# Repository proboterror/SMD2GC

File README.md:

# Sega Mega Drive to GameCube controller adapter

Also supports Xbox controllers (Xbox 360 / One / Series) and standard USB HID gamepads (with layout similar to PS4 DualShock 4) with USB Type-C OTG adapter.

USB gamepads support can be limited because of GameCube controller port does not provide sufficient +5V power (PS5 DualSense not working).

Bluetooth dongles are not supported unless they emulate standard USB HID device.

DualShock 3 / DualShock 4 / Xbox One / Series controllers are recommended.

Tested with USB controlers:

|Model|State|
|-----|-----|
|Xbox 360 USB|Working|
|Xbox One Model 1537|Working|
|Xbox Series Model 1914|Working|
|PS3 DualShock 3 CECHZC2R|Working|
|PS4 DualShock 4 CUH-ZCT1E|Working|
|PS5 DualSense CFI-ZCT1W|Not working<br>Unsufficient power|

## Schematics

## Bill of Materials
- GameCube controller replacement cable
- WaveShare RP2040-Zero board
- DB9 Male connector
- 12 wires (approx. 60 mm each); 3 wires for USB pads only

## Buttons mapping
A/B, X/Y buttons mapping for USB gamepads matches Xbox controllers layout (reverse SNES A/B, X/Y).

### Sega Mega Drive 6-button pad
src/main.cpp:
```
gc.a = smd.a;
gc.b = smd.b;
gc.x = smd.x;
gc.y = smd.y;

gc.l = smd.z;
gc.r = smd.c;

gc.start = smd.start;

gc.dLeft = smd.left;
gc.dRight = smd.right
gc.dDown = smd.down
gc.dUp = smd.up
gc.z = smd.mode
```
### Xbox controllers
src/main.c:
```
gc.a = (buttons & XINPUT_GAMEPAD_A);
gc.b = (buttons & XINPUT_GAMEPAD_B);
gc.x = (buttons & XINPUT_GAMEPAD_X);
gc.y = (buttons & XINPUT_GAMEPAD_Y);

gc.start = (buttons & (XINPUT_GAMEPAD_START | XINPUT_GAMEPAD_GUIDE));

gc.dLeft = (buttons & XINPUT_GAMEPAD_DPAD_LEFT);
gc.dRight = (buttons & XINPUT_GAMEPAD_DPAD_RIGHT);
gc.dDown = (buttons & XINPUT_GAMEPAD_DPAD_DOWN);
gc.dUp = (buttons & XINPUT_GAMEPAD_DPAD_UP);

const uint8_t TRIGGER_CLICK_TRESHOLD = 32;
gc.l = pad->bLeftTrigger > TRIGGER_CLICK_TRESHOLD
gc.r = pad->bRightTrigger > TRIGGER_CLICK_TRESHOLD;

gc.z = (buttons & XINPUT_GAMEPAD_RIGHT_SHOULDER);

gc.xStick = int16_to_u8_biased(pad->sThumbLX);
gc.yStick = int16_to_u8_biased(pad->sThumbLY);

gc.cxStick = int16_to_u8_biased(pad->sThumbRX);
gc.cyStick = int16_to_u8_biased(pad->sThumbRY);

gc.analogL = pad->bLeftTrigger;
gc.analogR = pad->bRightTrigger;
```

### Standard USB HID controllers (DualShock 4)
src/hid_gamecube_mapping.cpp:
```
REPORT_USAGE_PAGE_BUTTON, 1, MAP_GAMECUBE_BUTTON_X // Square -> X
REPORT_USAGE_PAGE_BUTTON, 2, MAP_GAMECUBE_BUTTON_A // Cross -> A
REPORT_USAGE_PAGE_BUTTON, 3, MAP_GAMECUBE_BUTTON_B // Circle -> B
REPORT_USAGE_PAGE_BUTTON, 4, MAP_GAMECUBE_BUTTON_Y // Triangle -> Y

REPORT_USAGE_PAGE_BUTTON, 6, MAP_GAMECUBE_BUTTON_Z // R1

// Note: DualShock S4 generates press event starting from minimum force,
// GameCube controller generates L/R clicks after maximum force to analog L/R axes applied.
// Can be replaced with mapping analog Rx/Ry axis with MAP_TYPE_THRESHOLD_ABOVE 192 (75%) to GameCube L/R.
REPORT_USAGE_PAGE_BUTTON, 7, MAP_GAMECUBE_BUTTON_L // L2 Digital
REPORT_USAGE_PAGE_BUTTON, 8, MAP_GAMECUBE_BUTTON_R // R2 Digital

REPORT_USAGE_PAGE_BUTTON, 10, MAP_GAMECUBE_BUTTON_START // Options -> Start

// Left analog
REPORT_USAGE_X, MAP_GAMECUBE_AXIS_X // LX
REPORT_USAGE_Y, MAP_GAMECUBE_AXIS_Y // LY, inverted
// Right analog
REPORT_USAGE_Z, MAP_GAMECUBE_AXIS_CX // RX 
REPORT_USAGE_Rz, MAP_GAMECUBE_AXIS_CY // RY, inverted
// Analog left/right triggers
REPORT_USAGE_Rx, MAP_GAMECUBE_AXIS_L // LT / R2
REPORT_USAGE_Ry, MAP_GAMECUBE_AXIS_R // RT / R2

// POV/HAT switch (also D-PAD in most cases)
// 0 on hat switch, just press up
MAP_GAMECUBE_U, HID_GAMEPAD_HAT_UP
// 1 on hat switch, press up and right
HID_GAMEPAD_HAT_UP_RIGHT, MAP_GAMECUBE_U
HID_GAMEPAD_HAT_UP_RIGHT, MAP_GAMECUBE_R
// 2 on hat switch, press right
HID_GAMEPAD_HAT_RIGHT, MAP_GAMECUBE_R
// 3 on hat, press right and down
HID_GAMEPAD_HAT_DOWN_RIGHT, MAP_GAMECUBE_R
HID_GAMEPAD_HAT_DOWN_RIGHT, MAP_GAMECUBE_D
// 4 on hat, press down
HID_GAMEPAD_HAT_DOWN, MAP_GAMECUBE_D
// 5 on hat, press down and left
HID_GAMEPAD_HAT_DOWN_LEFT, MAP_GAMECUBE_D
HID_GAMEPAD_HAT_DOWN_LEFT, MAP_GAMECUBE_L
// 6 on hat, press left
HID_GAMEPAD_HAT_LEFT, MAP_GAMECUBE_L
// 7 on hat, press left and up
HID_GAMEPAD_HAT_UP_LEFT, MAP_GAMECUBE_L
HID_GAMEPAD_HAT_UP_LEFT, MAP_GAMECUBE_U

// Rarely used
REPORT_USAGE_DPAD_UP, MAP_GAMECUBE_U
REPORT_USAGE_DPAD_DOWN, MAP_GAMECUBE_D
REPORT_USAGE_DPAD_RIGHT, MAP_GAMECUBE_R
REPORT_USAGE_DPAD_LEFT, MAP_GAMECUBE_L

PS4 DualShock 4 / PS5 DualSense used as reference for buttons IDs:
Button 0x01 - Square button
Button 0x02 - Cross button
Button 0x03 - Circle button
Button 0x04 - Triangle button
Button 0x05 - L1 button
Button 0x06 - R1 button
Button 0x07 - L2 button
Button 0x08 - R2 button
Button 0x09 - Share button
Button 0x0A - Options button
Button 0x0B - L3 button
Button 0x0C - R3 button
Button 0x0D - PS button
Button 0x0E - Touchpad button
```

### DualShock 3
```
gc.a = ps3->button_cross;
gc.b = ps3->button_circle;
gc.x = ps3->button_square;
gc.y = ps3->button_triangle;
gc.start = ps3->button_start;

gc.dLeft = ps3->dpad_left;
gc.dRight = ps3->dpad_right;
gc.dDown = ps3->dpad_down;
gc.dUp = ps3->dpad_up;

const uint8_t TRIGGER_CLICK_TRESHOLD = 32;
gc.l = ps3->trigger_l2_analog > TRIGGER_CLICK_TRESHOLD;
gc.r = ps3->trigger_r2_analog > TRIGGER_CLICK_TRESHOLD;

gc.z = ps3->trigger_r1;

gc.xStick = ps3->joy_left_x;
gc.yStick = UINT8_MAX - ps3->joy_left_y;
gc.cxStick = ps3->joy_right_x;
gc.cyStick = UINT8_MAX - ps3->joy_right_y;
gc.analogL = ps3->trigger_l2_analog;
gc.analogR = ps3->trigger_r2_analog;
```

## Input lag / latency
For Sega Mega Drive 6 buttons pad delay mostly defined by GameCube controller JoyBus speed if queried once per frame:<br>
3 bytes console request + 8 bytes response @250kbps: protocol delay ~0.35 ms.

USB pads are reports its state at fixed rate, mostly 125Hz (8 ms latency).<br>
DualShock 4 has a default wired polling rate 250Hz (4ms latency)<br>
Xbox Series Controller Model 1914: default USB poll rate 125Hz (8 ms latency)

## How to flash firmware
- Connect RP2040-Zero to PC
- Press BOOT and then RESET, new drive will appear
- Drop SMD2GC.uf2 from Releases section to new drive

## How to build firmware
Checkhout git repository.
```
git submodule update --init
```
Easy way:
- Install Visual Studio Code and official Raspberry Pi Pico Visual Studio Code extension
- On "Raspberry Pi Pico Project" left tab: "Import project"
- "Configure Cmake", use toolchain installed with Raspberry Pi Pico Visual Studio Code extension
- "Compile Project"
- "Run Project (USB)". Board should be in BOOT mode.

Hard way:
- Install Raspberry Pi Pico SDK, ARM-GCC toolchain, CMake.

## Credits
- [Julien Bernard](https://github.com/JulienBernard3383279/pico-rectangle) - Joybus protocol (Gamecube controller) implementation for the Raspberry Pi Pico
- [riguetti](https://github.com/riguetti/RP2040-Zero-gamecube-controller) - unused code cleanup
- [Andrew Tait](https://github.com/rasteri/HIDman) - USB HID descriptors and reports parsing code
- [Ryzee119](https://github.com/Ryzee119/tusb_xinput) - Xbox/Xinpit controllers support module for TinyUSB library

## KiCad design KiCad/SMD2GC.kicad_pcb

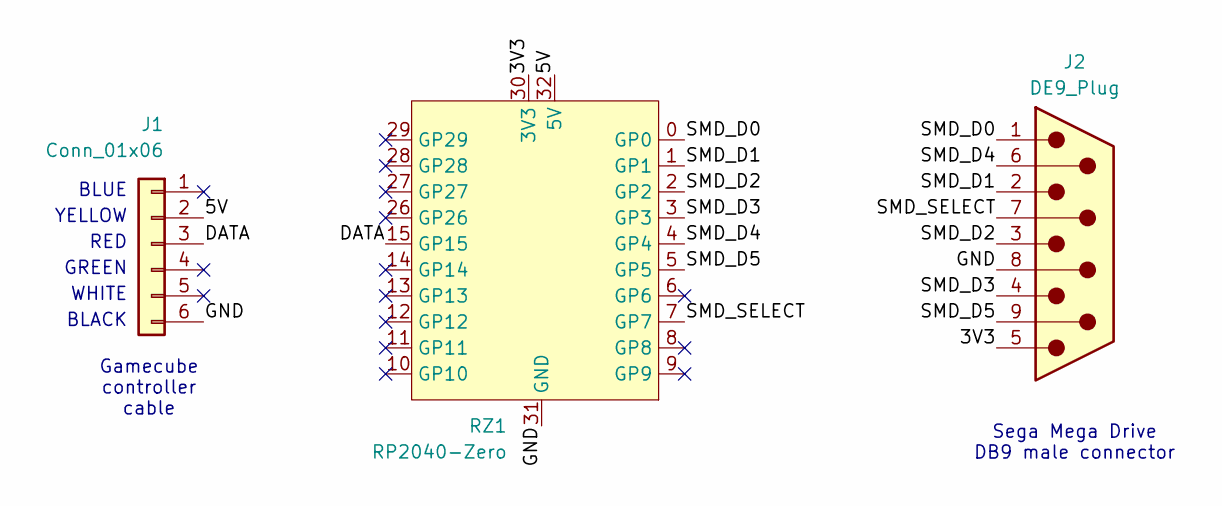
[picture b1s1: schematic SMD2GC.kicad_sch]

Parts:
J1: Conn_01x06; PinHeader_1x06_P2.00mm_Vertical
J2: DE9_Plug; DSUB-9_Male_Horizontal_P2.77x2.84mm_EdgePinOffset7.70mm_Hou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
RZ1: RP2040-Zero

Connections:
/3V3: J2.5, RZ1.30 (3V3)
/5V: J1.2, RZ1.32 (5V)
/DATA: J1.3, RZ1.15 (GP15)
/GND: J1.6, J2.8, RZ1.31 (GND)
/SMD_D0: J2.1, RZ1.0 (GP0)
/SMD_D1: J2.2, RZ1.1 (GP1)
/SMD_D2: J2.3, RZ1.2 (GP2)
/SMD_D3: J2.4, RZ1.3 (GP3)
/SMD_D4: J2.6, RZ1.4 (GP4)
/SMD_D5: J2.9, RZ1.5 (GP5)
/SMD_SELECT: J2.7, RZ1.7 (GP7)

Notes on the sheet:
YELLOW
WHITE
Sega Mega Drive DB9 male connector
BLUE
RED
Gamecube controller cable
BLACK
GREEN

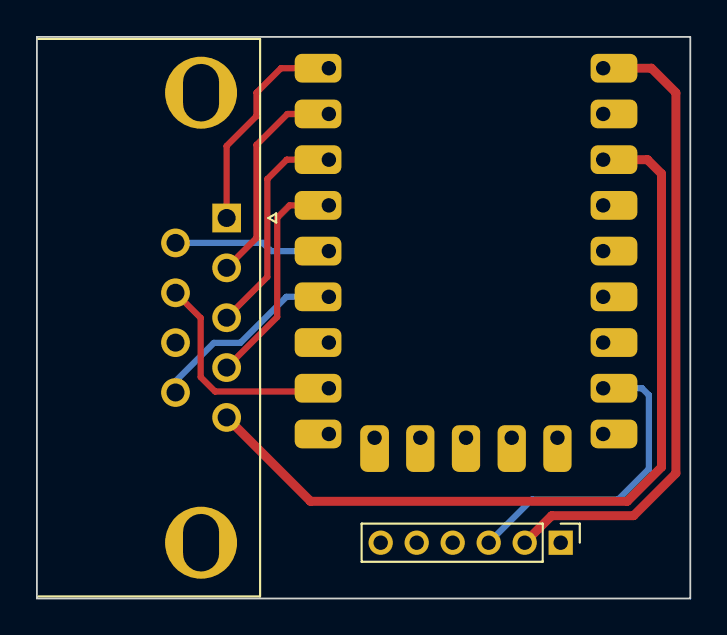
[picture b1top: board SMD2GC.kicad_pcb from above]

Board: 2 copper layers, 36.3 x 31.2 mm, 3 parts (1 on the bottom side), 11 nets.

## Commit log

2025-11-23 Implement Sega Mega Drive to Gamecube / Wii controller adapter firmware. 6-buttons and 3-buttons controllers supported.
    Delete unused code.
2025-11-23 Add KiCad schematic and draft PCB. RP2040-Zero symbol and footprint source: https://github.com/proboterror/Pentagon_128_Interface_Board
2025-11-23 Add project description.
2025-11-23 Update README.md.
2025-12-05 Add xinput USB controllers support with https://github.com/Ryzee119/tusb_xinput library. Xbox 360, Xbox One / Series controllers are supported.
    Add TinyUSB library with hardware host enabled.
    Set cores clock to 150 MHz as recommended for stable USB host support. JoyBus pio program clock divider updated to keep 25 MHz clock.
    Enable stdio uart support for USB devices debugging at pins tx/rx 8/9, 115200 baud. Disable stdio over USB.
    Sega Mega Drive controller support: pullup data gpio pins by default for correct gamepad presence detection.
2025-12-05 Add USB HID gamepads support. HID to GameCube mapping for PS4 DualShock 4 / PS4 DualSense layout.
    Added HID report descriptors / reports parsing / mapping library for HID gamepad / keyboad / mouse, based on https://github.com/rasteri/HIDman
    Add library unit tests and sample data, targeting Visual Studio and Windows platform (src/CMakeLists.txt).
    Test data source: own dumps if not specified.
    Tested with hardware (WaveShare RP2040-Zero with Wii GameCube controller port, rumble +5V for board / USB VBUS power):
    PS4 DualShock 4 (CUH-ZCT1E): working without issues.
    PS5 DualSense (CFI-ZCT1W): not detected, insufficient power. Working with external +5V power.
2025-12-05 Update project description.
2025-12-05 Update schematic for USB VBUS +5V power from GameCube rumble power.
2025-12-06 Invert right/left Y axes for HID gamepads (DualShock 4).
2025-12-06 PS3 DualShock 3 custom driver implemented.
    Invert analog Y axes for HID gamepads (checked with DualShock 4).
2025-12-06 More correct report parsing error handling: - Always queue new report request - Parse HID reports only for standard HID devices with successfully parsed report descriptors
2025-12-07 Sync DualShock / DualSense controllers A/B, X/Y buttons mapping with Xinput gamepads layout (reverse SNES A/B, X,Y).
2025-12-07 Move out Sega gamepad state to GameCube mapping to main.cpp.
